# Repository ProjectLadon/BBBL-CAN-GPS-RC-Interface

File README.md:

# BBBL-CAN-GPS-RC-Interface
Boards for interfacing GPS, CAN, and SBUS to a Beaglebone Blue.

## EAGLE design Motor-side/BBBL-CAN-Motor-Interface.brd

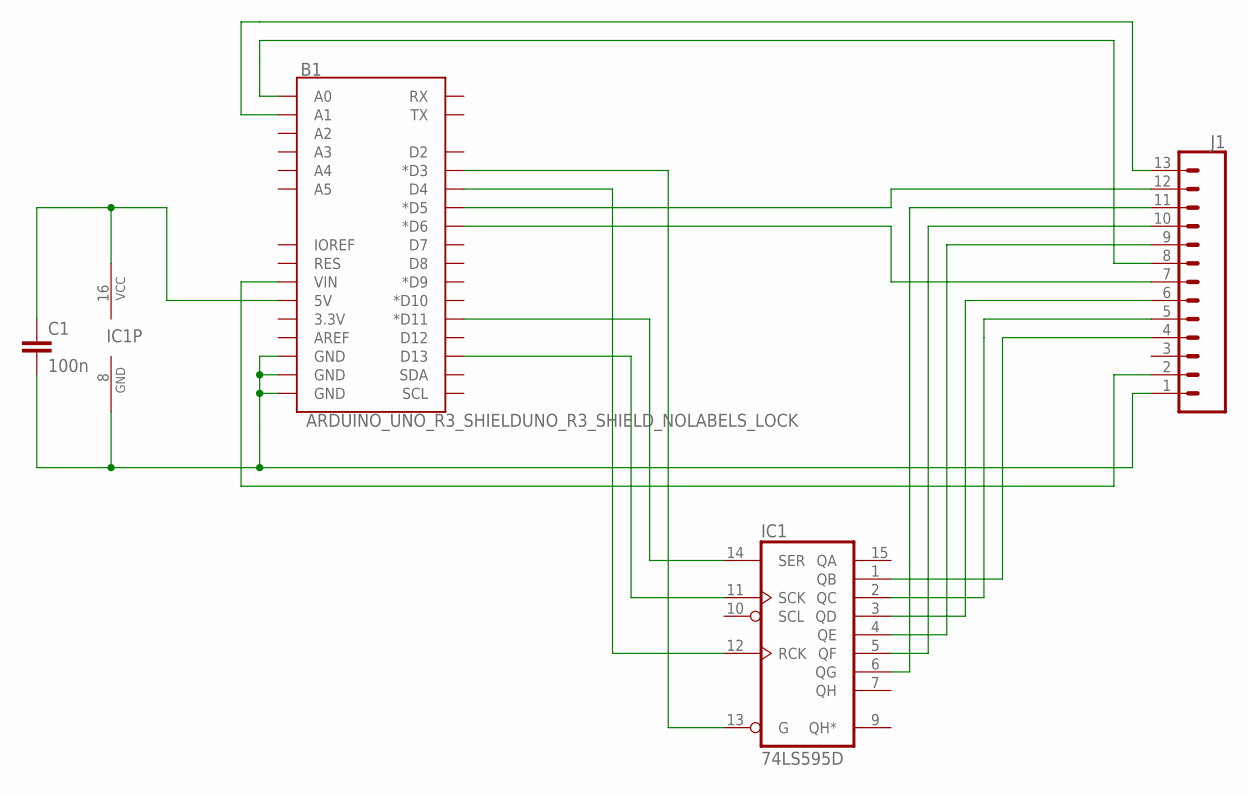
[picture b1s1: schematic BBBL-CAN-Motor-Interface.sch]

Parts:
B1: ARDUINO_UNO_R3_SHIELDUNO_R3_SHIELD_NOLABELS_LOCK; UNO_R3_SHIELD_NOLABELS_LOCK
C1: 100n; C0603
IC1: 74LS595D; SO16
J1: CONN_13LOCK; 1X13_LOCK

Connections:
GND: B1.GND@0 (GND), B1.GND@1 (GND), B1.GND@2 (GND), C1.2, IC1.8 (GND), J1.1
unnamed: B1.D5 (*D5), J1.12
unnamed: B1.A0, J1.8
unnamed: B1.A1, J1.13
unnamed: B1.D6 (*D6), J1.7
unnamed: IC1.6 (QG), J1.11
unnamed: IC1.5 (QF), J1.10
unnamed: IC1.4 (QE), J1.9
unnamed: IC1.3 (QD), J1.6
unnamed: IC1.2 (QC), J1.5
unnamed: IC1.1 (QB), J1.4
unnamed: B1.D3 (*D3), IC1.13 (G)
unnamed: B1.VIN, J1.2
unnamed: B1.D11 (*D11), IC1.14 (SER)
unnamed: B1.D13, IC1.11 (SCK)
unnamed: B1.D4, IC1.12 (RCK)
unnamed: B1.5V, C1.1, IC1.16 (VCC)

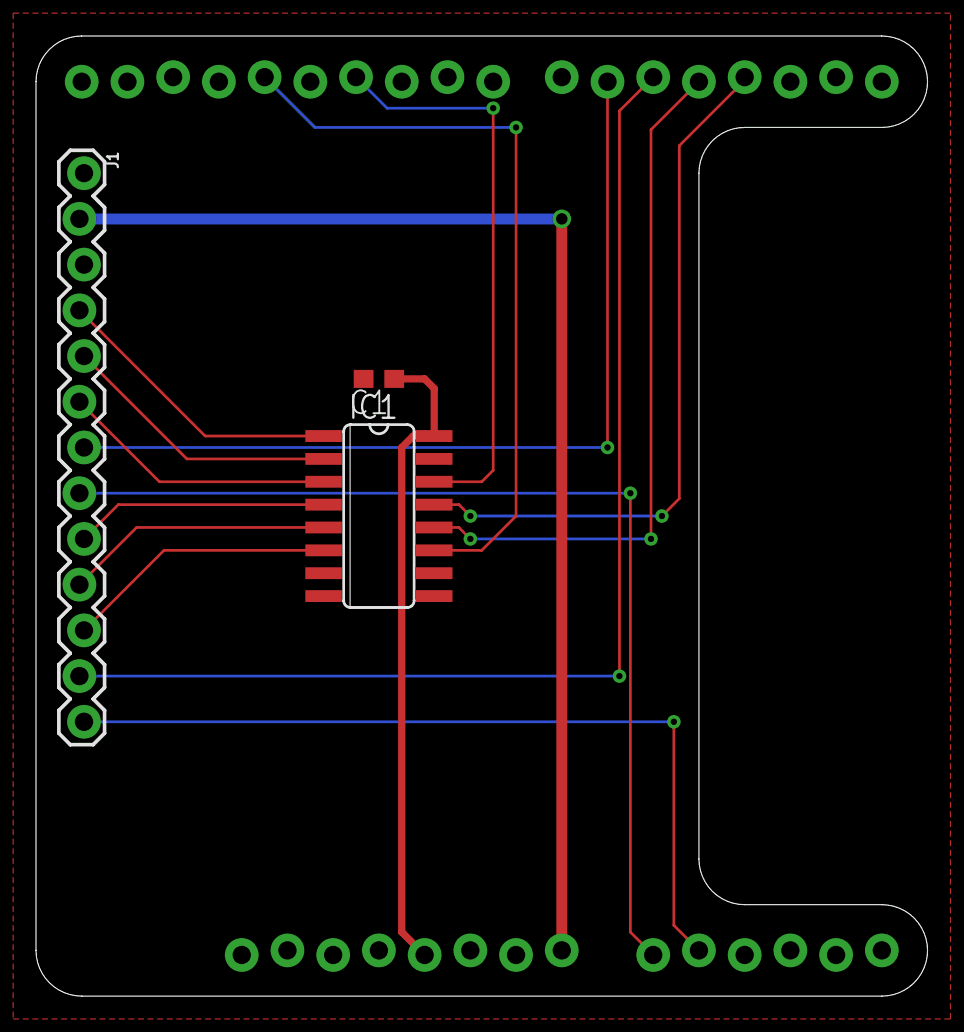
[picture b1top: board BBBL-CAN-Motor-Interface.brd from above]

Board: 2 copper layers, 49.5 x 53.3 mm, 4 parts (0 on the bottom side), 17 nets.

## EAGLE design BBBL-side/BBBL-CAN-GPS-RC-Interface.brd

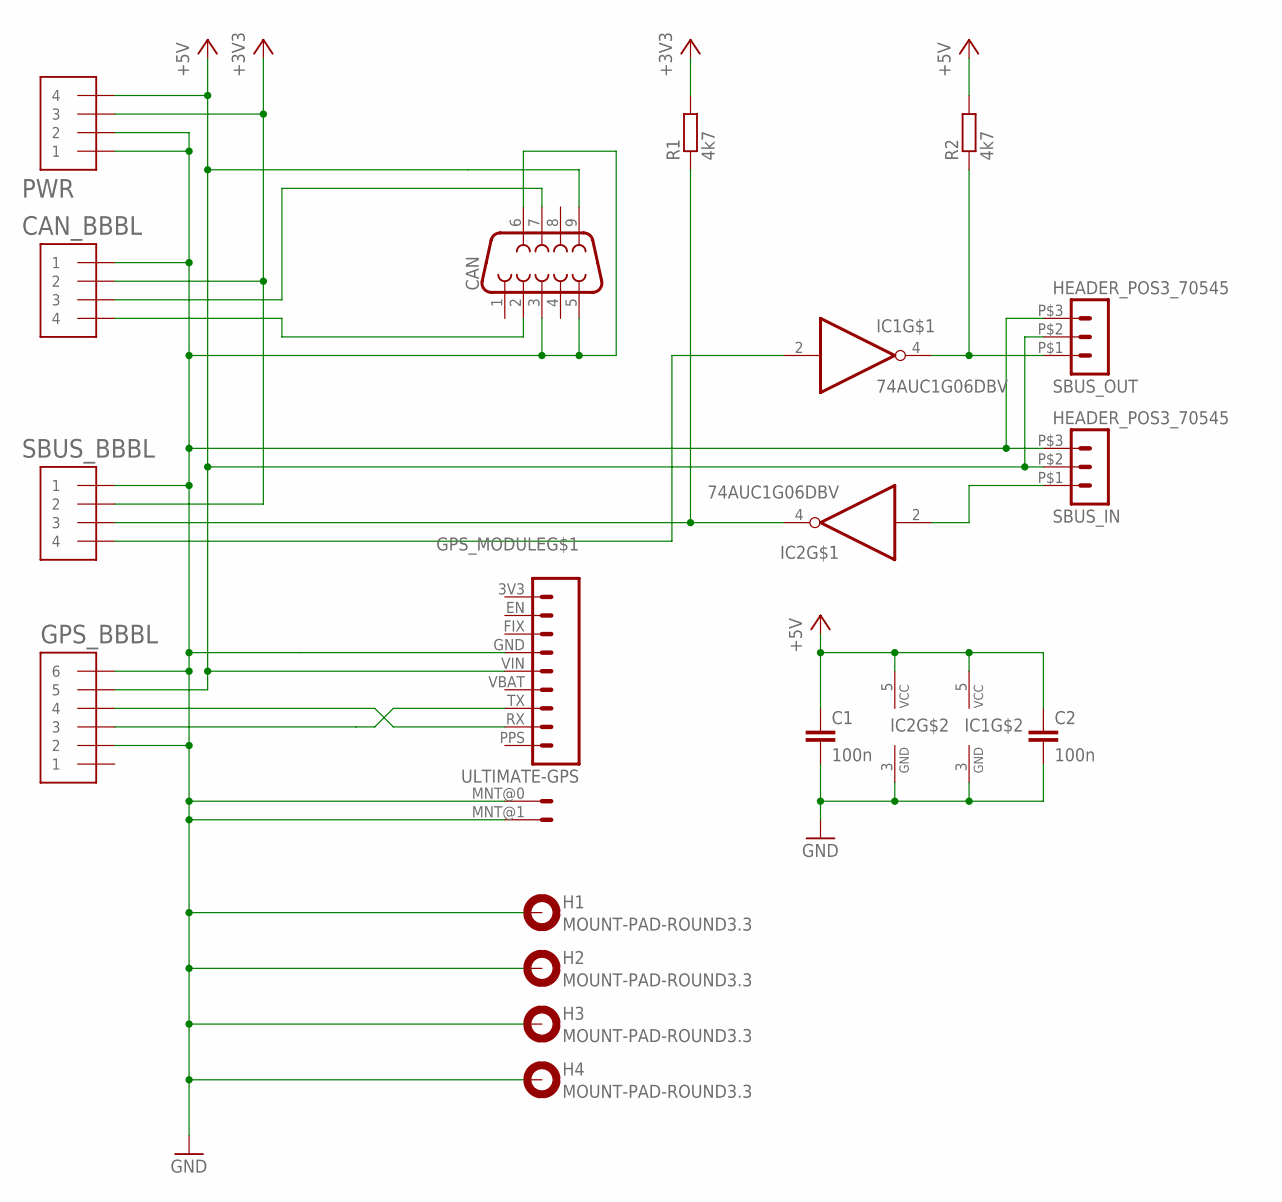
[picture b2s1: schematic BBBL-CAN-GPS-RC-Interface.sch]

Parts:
C1, C2: 100n; C0603
CAN: DB9MALE; DB9_MALE
CAN_BBBL: STRAWSON_EAGLE_LIB_JST_SH_4; STRAWSON_EAGLE_LIB_JST_SH_4_SMD
GPS_BBBL: STRAWSON_EAGLE_LIB_JST_SH_6
GPS_MODULE: ULTIMATE-GPS
H1, H2, H3, H4: MOUNT-PAD-ROUND3.3; 3,3-PAD
IC1, IC2: 74AUC1G06DBV; SOT23-5
PWR: STRAWSON_EAGLE_LIB_JST_SH_4; STRAWSON_EAGLE_LIB_JST_SH_4_SMD
R1, R2: 4k7; R0603
SBUS_BBBL: STRAWSON_EAGLE_LIB_JST_SH_4; STRAWSON_EAGLE_LIB_JST_SH_4_SMD
SBUS_IN: HEADER_POS3_70545; 70545-POS3
SBUS_OUT: HEADER_POS3_70545; 70545-POS3

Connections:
+3V3: CAN_BBBL.2, PWR.3, R1.2, SBUS_BBBL.2
+5V: C1.1, C2.1, CAN.9, GPS_BBBL.5, GPS_MODULE.VIN (5), IC1.5 (VCC), IC2.5 (VCC), PWR.4, R2.2, SBUS_IN.P$2 (2), SBUS_OUT.P$2 (2)
GND: C1.2, C2.2, CAN.3, CAN.5, CAN.6, CAN_BBBL.1, GPS_BBBL.2, GPS_BBBL.6, GPS_MODULE.GND (6), GPS_MODULE.MNT@0 (9), GPS_MODULE.MNT@1 (9), H1.B3,3, H2.B3,3, H3.B3,3, H4.B3,3, IC1.3 (GND), IC2.3 (GND), PWR.1, PWR.2, SBUS_BBBL.1, SBUS_IN.P$3 (3), SBUS_OUT.P$3 (3)
unnamed: GPS_BBBL.3, GPS_MODULE.TX (3)
unnamed: GPS_BBBL.4, GPS_MODULE.RX (2)
unnamed: CAN.7, CAN_BBBL.3
unnamed: CAN.2, CAN_BBBL.4
unnamed: IC2.4 (O), R1.1, SBUS_BBBL.3
unnamed: IC2.2 (I), SBUS_IN.P$1 (1)
unnamed: IC1.4 (O), R2.1, SBUS_OUT.P$1 (1)
unnamed: IC1.2 (I), SBUS_BBBL.4

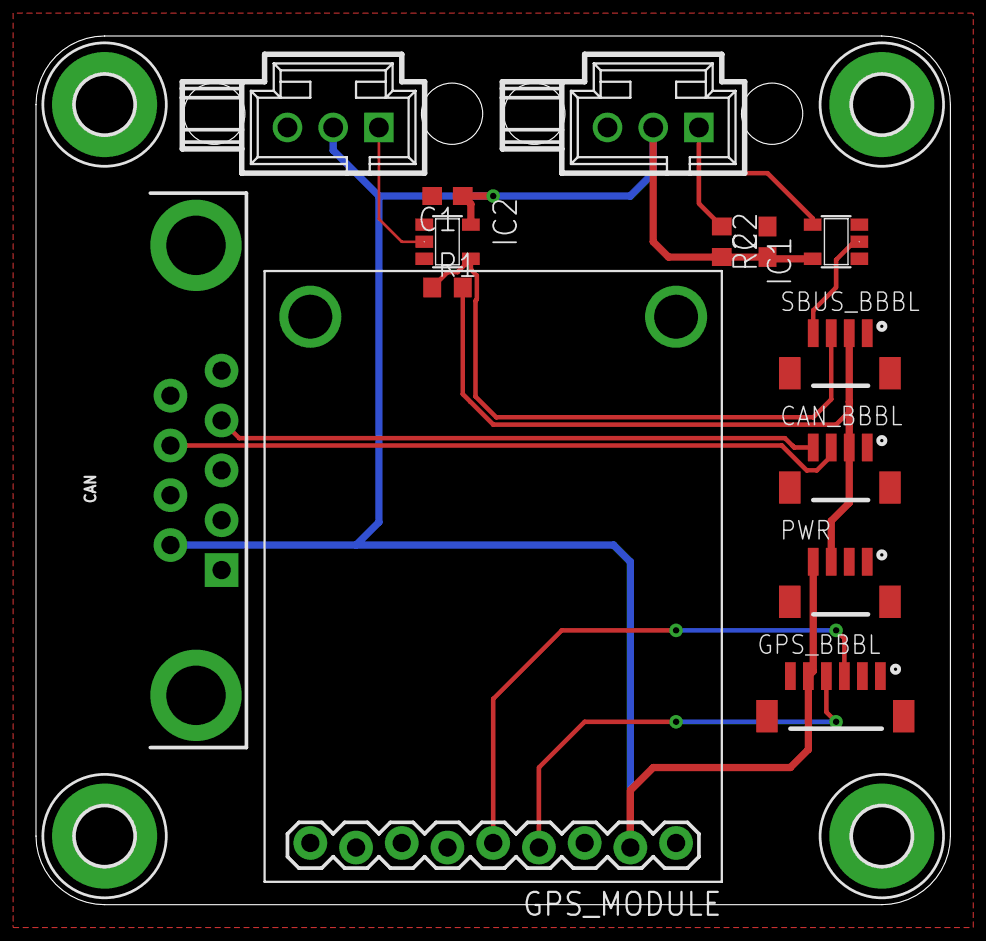
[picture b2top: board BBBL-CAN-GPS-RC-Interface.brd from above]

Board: 2 copper layers, 50.8 x 48.3 mm, 18 parts (0 on the bottom side), 11 nets.

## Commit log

2018-07-29 Moved original interface board and added a new interface board for plugging a Pololu dual VNH5019 shield into a stack
2018-07-29 Modified Motor interface for non-interference with the CAN shield.

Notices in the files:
parts and their libraries:
SparkFun-Connectors: Licensing: Creative Commons ShareAlike 4.0 International - https://creativecommons.org/licenses/by-sa/4.0
